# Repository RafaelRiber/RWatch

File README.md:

# RWatch
 
  <p align="center">
 
 <em>Early render of the watch</em>
 
## Short description
The RWatch is a modern and elegant oled "smartwatch" based around the Atmel ATSAMD21-G18A ARM Cortex M0+ Microcontroller, with a 9 DOF IMU and environmental sensing, and everything contained in a PCB the size of the screen.

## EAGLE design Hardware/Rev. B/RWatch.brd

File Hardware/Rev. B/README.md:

### Warning ! Rev B has not been tested. Use at your own risk

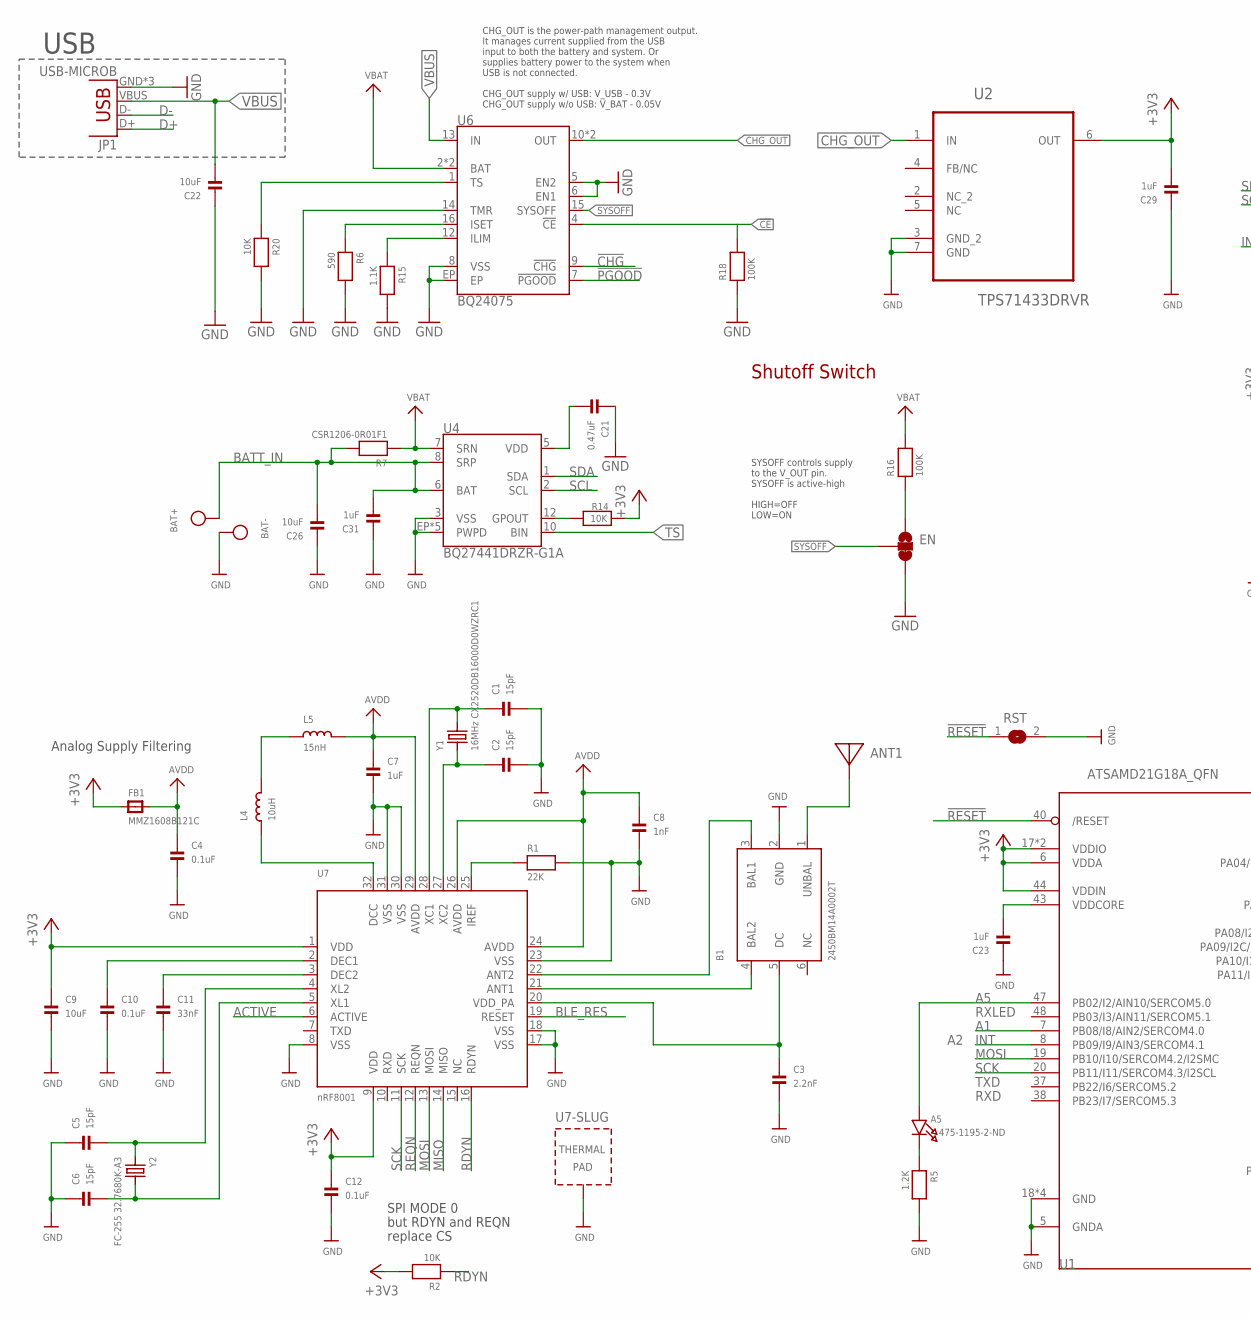
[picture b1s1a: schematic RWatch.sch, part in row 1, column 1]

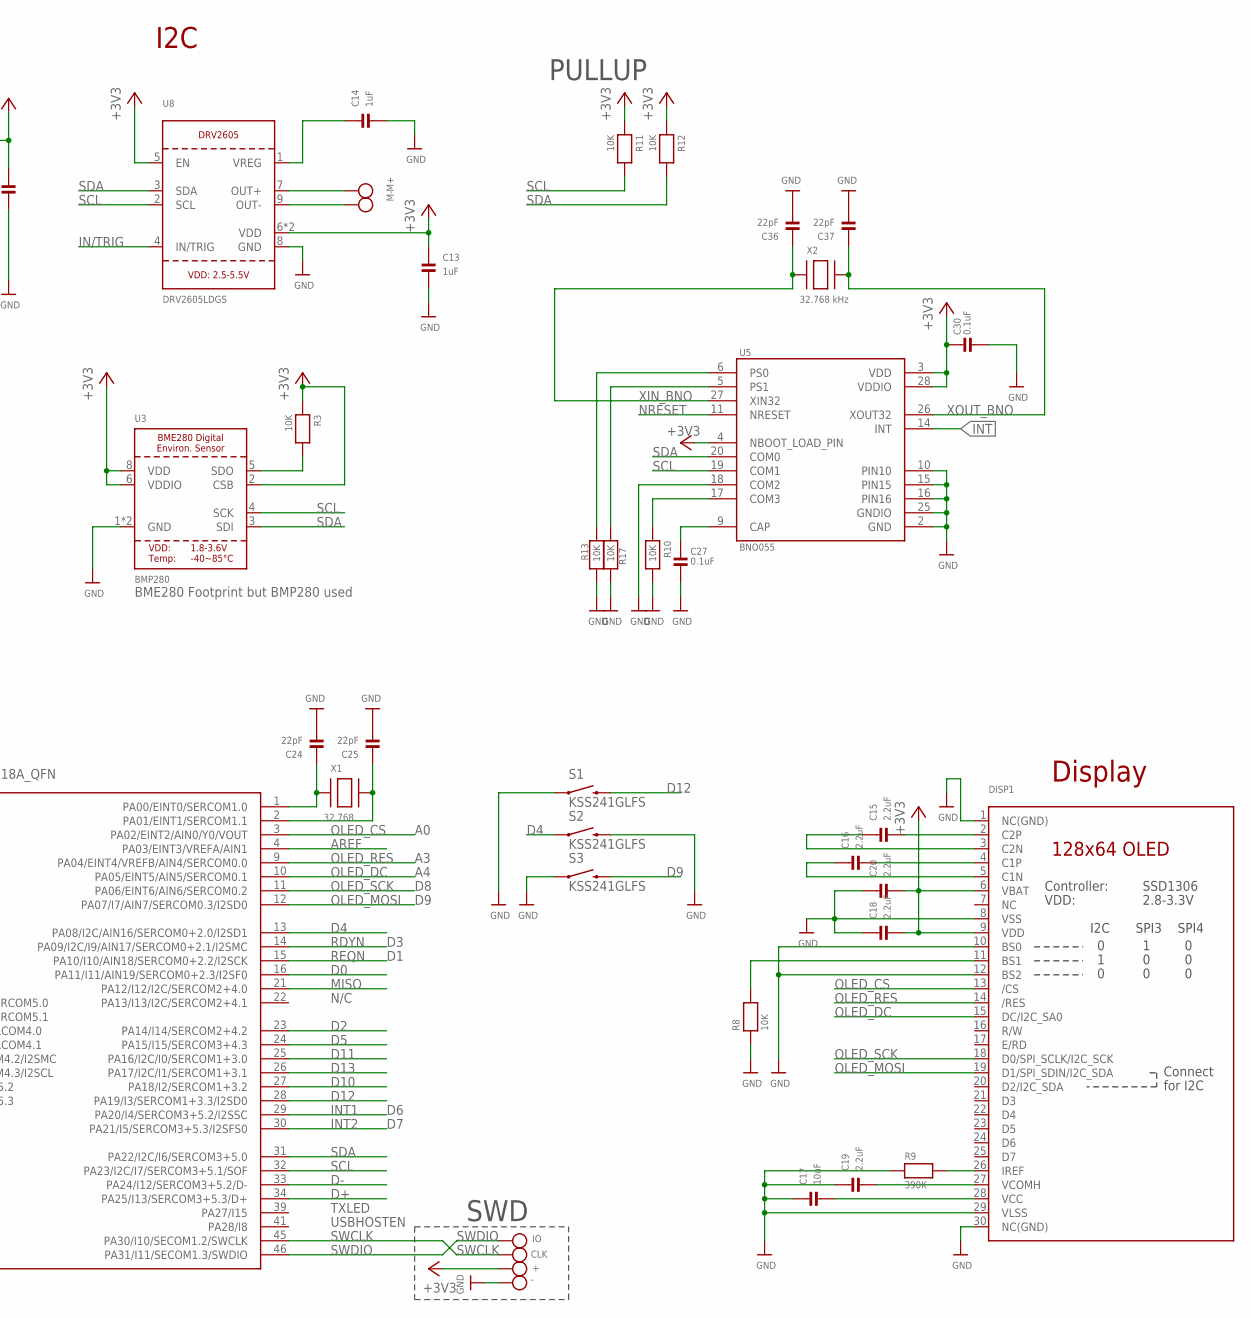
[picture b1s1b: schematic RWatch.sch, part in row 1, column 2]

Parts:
+: TESTPOINTROUND1.5MM; TESTPOINT_ROUND_1.5MM
-: TESTPOINTROUND1.5MM; TESTPOINT_ROUND_1.5MM
A5: 475-1195-2-ND; CHIPLED_0603_NOOUTLINE
ANT1: ANTENNA_PCBNRF8001_1.6MM; ANT_PCB_2.4GHZ_NRF8001_1.6MM_1OZ
B1: 2450BM14A0002T; BALUN0603
BAT+: TESTPOINTROUND2MM; TESTPOINT_ROUND_2MM
BAT-: TESTPOINTROUND2MM; TESTPOINT_ROUND_2MM
C1, C2, C5, C6: 15pF; 0402
C3: 2.2nF; 0402
C4, C10, C12, C27, C30: 0.1uF; 0402
C7, C13, C14, C23, C29, C31: 1uF; 0402
C8: 1nF; 0402
C9: 10uF; 0402
C11: 33nF; 0402
C15, C16, C18, C19, C20: 2.2uF; 0402
C17, C22, C26: 10uF; 0603
C21: 0.47uF; 0402
C24, C25, C36, C37: 22pF; 0402
CLK: TESTPOINTROUND1.5MM; TESTPOINT_ROUND_1.5MM
DISP1: DISP_OLED_UG-2864HSWEG01; UG-2864HSWEG01_1.3_WRAPAROUND
EN: JUMPER-PAD-3-2OF3_NC_BY_TRACE_SMALL; PAD-JUMPER-3-2OF3_NC_BY_TRACE_YES_SILK_FULL_BOX
FB1: MMZ1608B121C; 0805
IO: TESTPOINTROUND1.5MM; TESTPOINT_ROUND_1.5MM
JP1: USB-MICROB; MPN 10104110-0001LF
L4: 10uH; _0603
L5: 15nH; _0603
M+: TESTPOINTROUND2MM; TESTPOINT_ROUND_2MM
M-: TESTPOINTROUND2MM; TESTPOINT_ROUND_2MM
R1: 22K; 0402
R2, R8: 10K; 0402
R3, R10, R11, R12, R13, R14, R17, R20: 10K; 0402; MPN CRCW060310K0FKEA
R5: 1.2K; 0402; MPN MC0063W06031221R
R6: 590; 0402; MPN CRCW060310K0FKEA
R7: CSR1206-0R01F1; 1206
R9: 390K; 0402
R15: 1.1K; 0402; MPN CRCW060310K0FKEA
R16, R18: 100K; 0402; MPN MC0063W06031221R
RST: SOLDERJUMPERREFLOW; SOLDERJUMPER_REFLOW
S1, S2, S3: KSS241GLFS
U1: ATSAMD21G18A_QFN; TQFN48_7MM
U2: TPS71433DRVR; SON65P200X200X80-7N
U3: BMP280; BME280
U4: BQ27441DRZR-G1A; PDSO-N12
U5: BNO055; LGA28R50P4X10_380X520X100
U6: BQ24075; PVQFN-N16
U7: nRF8001; QFN32_5MM
U8: DRV2605LDGS; PSOP10
X1: 32.768; XTAL3215
X2: 32.768 kHz; XTAL3215
Y1: 16MHz CX2520DB16000D0WZRC1; CRYSTAL_2.5X2
Y2: FC-255 32.7680K-A3; CRYSTAL_4.9X1.8

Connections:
!CE!: R18.2, U6.4 (!CE!)
!CHG!: U6.9 (!CHG!)
!PGOOD!: U6.7 (!PGOOD!)
!RESET: RST.1, U1.40 (/RESET)
+3V3: +.P$1, C9.1, C12.1, C13.1, C18.2, C20.2, C29.2, C30.2, DISP1.6 (VBAT), DISP1.9 (VDD), FB1.1, R2.2, R3.1, R11.1, R12.1, R14.1, U1.6 (VDDA), U1.17 (VDDIO), U1.36 (VDDIO), U1.44 (VDDIN), U2.6 (OUT), U3.2 (CSB), U3.6 (VDDIO), U3.8 (VDD), U5.3 (VDD), U5.4 (NBOOT_LOAD_PIN), U5.28 (VDDIO), U7.1 (VDD), U7.9 (VDD), U8.5 (EN), U8.6 (VDD), U8.10 (VDD)
A1: U1.7 (PB08/I8/AIN2/SERCOM4.0)
A5: A5.A, U1.47 (PB02/I2/AIN10/SERCOM5.0)
ACTIVE: U7.6 (ACTIVE)
AREF: U1.4 (PA03/EINT3/VREFA/AIN1)
AVDD: C4.1, C7.1, C8.1, FB1.2, L5.2, U7.24 (AVDD), U7.26 (AVDD), U7.29 (AVDD)
BATT_IN: BAT+.P$1, C26.2, C31.2, R7.2, U4.6 (BAT), U4.8 (SRP)
BLE_RES: U7.19 (RESET)
CHG_OUT: U2.1 (IN), U6.10 (OUT), U6.11 (OUT)
D0: U1.16 (PA11/I11/AIN19/SERCOM0+2.3/I2SF0)
D2: U1.23 (PA14/I14/SERCOM2+4.2)
D4: S2.1, U1.13 (PA08/I2C/AIN16/SERCOM0+2.0/I2SD1)
D5: U1.24 (PA15/I15/SERCOM3+4.3)
D9: S3.2
D10: U1.27 (PA18/I2/SERCOM1+3.2)
D11: U1.25 (PA16/I2C/I0/SERCOM1+3.0)
D12: S1.2, U1.28 (PA19/I3/SERCOM1+3.3/I2SD0)
D13: U1.26 (PA17/I2C/I1/SERCOM1+3.1)
D+: JP1.D+, U1.34 (PA25/I13/SERCOM3+5.3/D+)
D-: JP1.D-, U1.33 (PA24/I12/SERCOM3+5.2/D-)
GND: -.P$1, B1.2 (GND), BAT-.P$1, C1.2, C2.2, C3.2, C4.2, C5.1, C6.1, C7.2, C8.2, C9.2, C10.2, C11.2, C12.2, C13.2, C14.2, C17.1, C18.1, C19.1, C20.1, C21.1, C22.1, C23.1, C24.2, C25.2, C26.1, C27.1, C29.1, C30.1, C31.1, C36.2, C37.2, DISP1.1 (NC(GND)), DISP1.8 (VSS), DISP1.10 (BS0), DISP1.12 (BS2), DISP1.29 (VLSS), DISP1.30 (NC(GND)), EN.3, JP1.GND, JP1.MT1 (GND), JP1.MT2 (GND), R1.2, R5.2, R6.2, R8.1, R9.1, R10.2, R13.2, R15.2, R17.2, R18.1, R20.2, RST.2, S1.1, S2.2, S3.1, U1.5 (GNDA), U1.18 (GND), U1.35 (GND), U1.42 (GND), U1.THERMAL (GND), U2.3 (GND_2), U2.7 (GND), U3.1 (GND), U3.7 (GND), U4.3 (VSS), U4.EP (PWPD), U4.EP1 (PWPD), U4.EP2 (PWPD), U4.EP3 (PWPD), U4.EP4 (PWPD), U5.2 (GND), U5.10 (PIN10), U5.15 (PIN15), U5.16 (PIN16), U5.18 (COM2), U5.25 (GNDIO), U6.5 (EN2), U6.6 (EN1), U6.8 (VSS), U6.14 (TMR), U6.EP, U7.8 (VSS), U7.17 (VSS), U7.18 (VSS), U7.23 (VSS), U7.30 (VSS), U7.31 (VSS), U7.33 (TP), U8.8 (GND)
ILIM: R15.1, U6.12 (ILIM)
IN/TRIG: U8.4 (IN/TRIG)
INT: U1.8 (PB09/I9/AIN3/SERCOM4.1), U5.14 (INT)
INT1: U1.29 (PA20/I4/SERCOM3+5.2/I2SSC)
INT2: U1.30 (PA21/I5/SERCOM3+5.3/I2SFS0)
ISET: R6.1, U6.16 (ISET)
MISO: U1.21 (PA12/I12/I2C/SERCOM2+4.0), U7.14 (MISO)
MOSI: U1.19 (PB10/I10/SERCOM4.2/I2SMC), U7.13 (MOSI)
unnamed: ANT1.FEED, B1.1 (UNBAL)
unnamed: B1.3 (BAL1), U7.22 (ANT2)
unnamed: B1.4 (BAL2), U7.21 (ANT1)
unnamed: B1.5 (DC), C3.1, U7.20 (VDD_PA)
unnamed: L4.2, L5.1
unnamed: DISP1.11 (BS1), R8.2
unnamed: C11.1, U7.3 (DEC2)
unnamed: C10.1, U7.2 (DEC1)
unnamed: C1.1, U7.28 (XC1), Y1.3 (2)
unnamed: C2.1, U7.27 (XC2), Y1.1
unnamed: L4.1, U7.32 (DCC)
unnamed: R1.1, U7.25 (IREF)
unnamed: C21.2, U4.5 (VDD)
unnamed: C24.1, U1.1 (PA00/EINT0/SERCOM1.0), X1.P$1
unnamed: C25.1, U1.2 (PA01/EINT1/SERCOM1.1), X1.P$2
unnamed: R3.2, U3.5 (SDO)
unnamed: C14.1, U8.1 (VREG)
unnamed: R14.2, U4.12 (GPOUT)
unnamed: C5.2, U7.4 (XL2), Y2.1
unnamed: C6.2, U7.5 (XL1), Y2.2
unnamed: EN.1, R16.1
unnamed: A5.C, R5.1
unnamed: C27.2, U5.9 (CAP)
unnamed: R10.1, U5.17 (COM3)
unnamed: R17.1, U5.5 (PS1)
unnamed: R13.1, U5.6 (PS0)
unnamed: DISP1.26 (IREF), R9.2
unnamed: C15.2, DISP1.2 (C2P)
unnamed: C15.1, DISP1.3 (C2N)
unnamed: C16.2, DISP1.4 (C1P)
unnamed: C16.1, DISP1.5 (C1N)
unnamed: C17.2, DISP1.28 (VCC)
unnamed: C19.2, DISP1.27 (VCOMH)
NRESET: U5.11 (NRESET)
OLED_CS: DISP1.13 (/CS), U1.3 (PA02/EINT2/AIN0/Y0/VOUT)
OLED_DC: DISP1.15 (DC/I2C_SA0), U1.10 (PA05/EINT5/AIN5/SERCOM0.1)
OLED_MOSI: DISP1.19 (D1/SPI_SDIN/I2C_SDA), U1.12 (PA07/I7/AIN7/SERCOM0.3/I2SD0)
OLED_RES: DISP1.14 (/RES), U1.9 (PA04/EINT4/VREFB/AIN4/SERCOM0.0)
OLED_SCK: DISP1.18 (D0/SPI_SCLK/I2C_SCK), U1.11 (PA06/EINT6/AIN6/SERCOM0.2)
OUT+: M+.P$1, U8.7 (OUT+)
OUT-: M-.P$1, U8.9 (OUT-)
RDYN: R2.1, U1.14 (PA09/I2C/I9/AIN17/SERCOM0+2.1/I2SMC), U7.16 (RDYN)
REQN: U1.15 (PA10/I10/AIN18/SERCOM0+2.2/I2SCK), U7.12 (REQN)
SCK: U1.20 (PB11/I11/SERCOM4.3/I2SCL), U7.11 (SCK)
SCL: R11.2, U1.32 (PA23/I2C/I7/SERCOM3+5.1/SOF), U3.4 (SCK), U4.2 (SCL), U5.19 (COM1), U8.2 (SCL)
SDA: R12.2, U1.31 (PA22/I2C/I6/SERCOM3+5.0), U3.3 (SDI), U4.1 (SDA), U5.20 (COM0), U8.3 (SDA)
SWCLK: CLK.P$1, U1.45 (PA30/I10/SECOM1.2/SWCLK)
SWDIO: IO.P$1, U1.46 (PA31/I11/SECOM1.3/SWDIO)
SYSOFF: EN.2, U6.15 (SYSOFF)
TS: R20.1, U4.10 (BIN), U6.1 (TS)
VBAT: R7.1, R16.2, U4.7 (SRN), U6.2 (BAT), U6.3 (BAT)
VBUS: C22.2, JP1.VBUS, U6.13 (IN)
VDDCORE1: C23.2, U1.43 (VDDCORE)
XIN_BNO: C36.1, U5.27 (XIN32), X2.P$1
XOUT_BNO: C37.1, U5.26 (XOUT32), X2.P$2

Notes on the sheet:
Analog Supply Filtering
SPI MODE 0
but RDYN and REQN
replace CS
SWD
Display
PULLUP
N/C
TXLED
USBHOSTEN
RXLED
TXD
RXD
USB
I2C
CHG_OUT is the power-path management output. It manages current supplied from the USB input to both the battery and system. Or supplies battery power to the system when USB is not connected. CHG_OUT supply w/ USB: V_USB - 0.3V CHG_OUT supply w/o USB: V_BAT - 0.05V
Shutoff Switch
SYSOFF controls supply to the V_OUT pin. SYSOFF is active-high HIGH=OFF LOW=ON
BME280 Footprint but BMP280 used

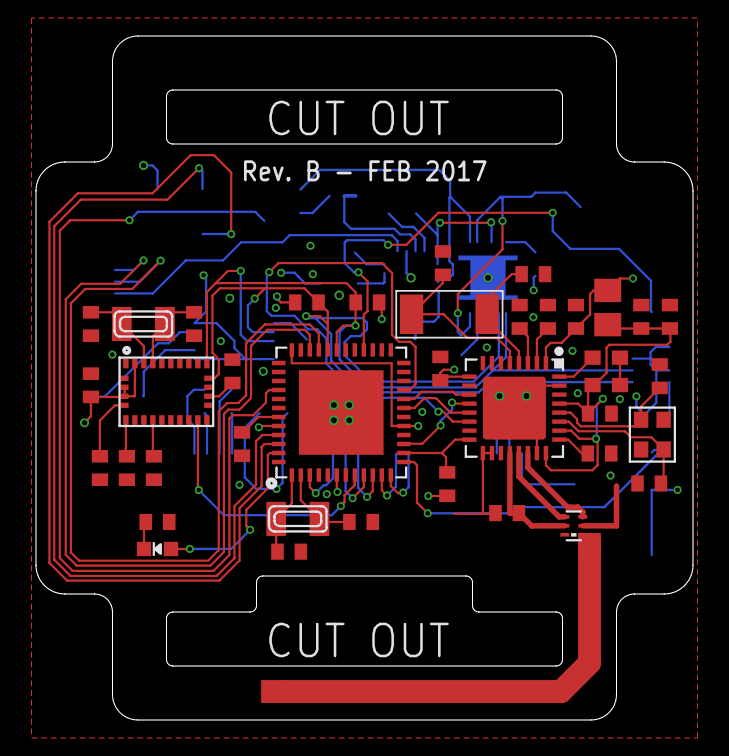
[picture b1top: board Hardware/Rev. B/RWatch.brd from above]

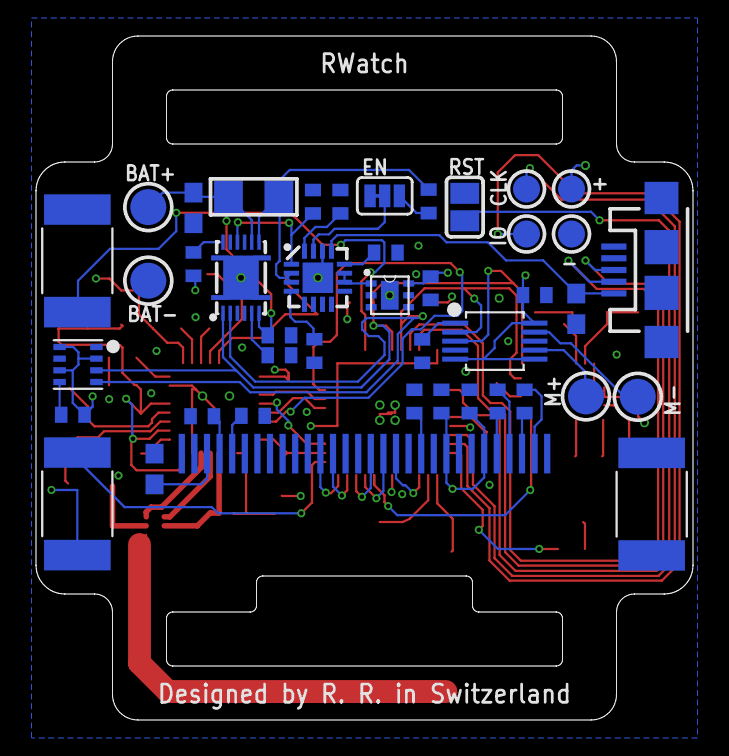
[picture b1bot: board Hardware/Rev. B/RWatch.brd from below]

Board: 4 copper layers, 36.5 x 38.0 mm, 83 parts (42 on the bottom side), 71 nets.

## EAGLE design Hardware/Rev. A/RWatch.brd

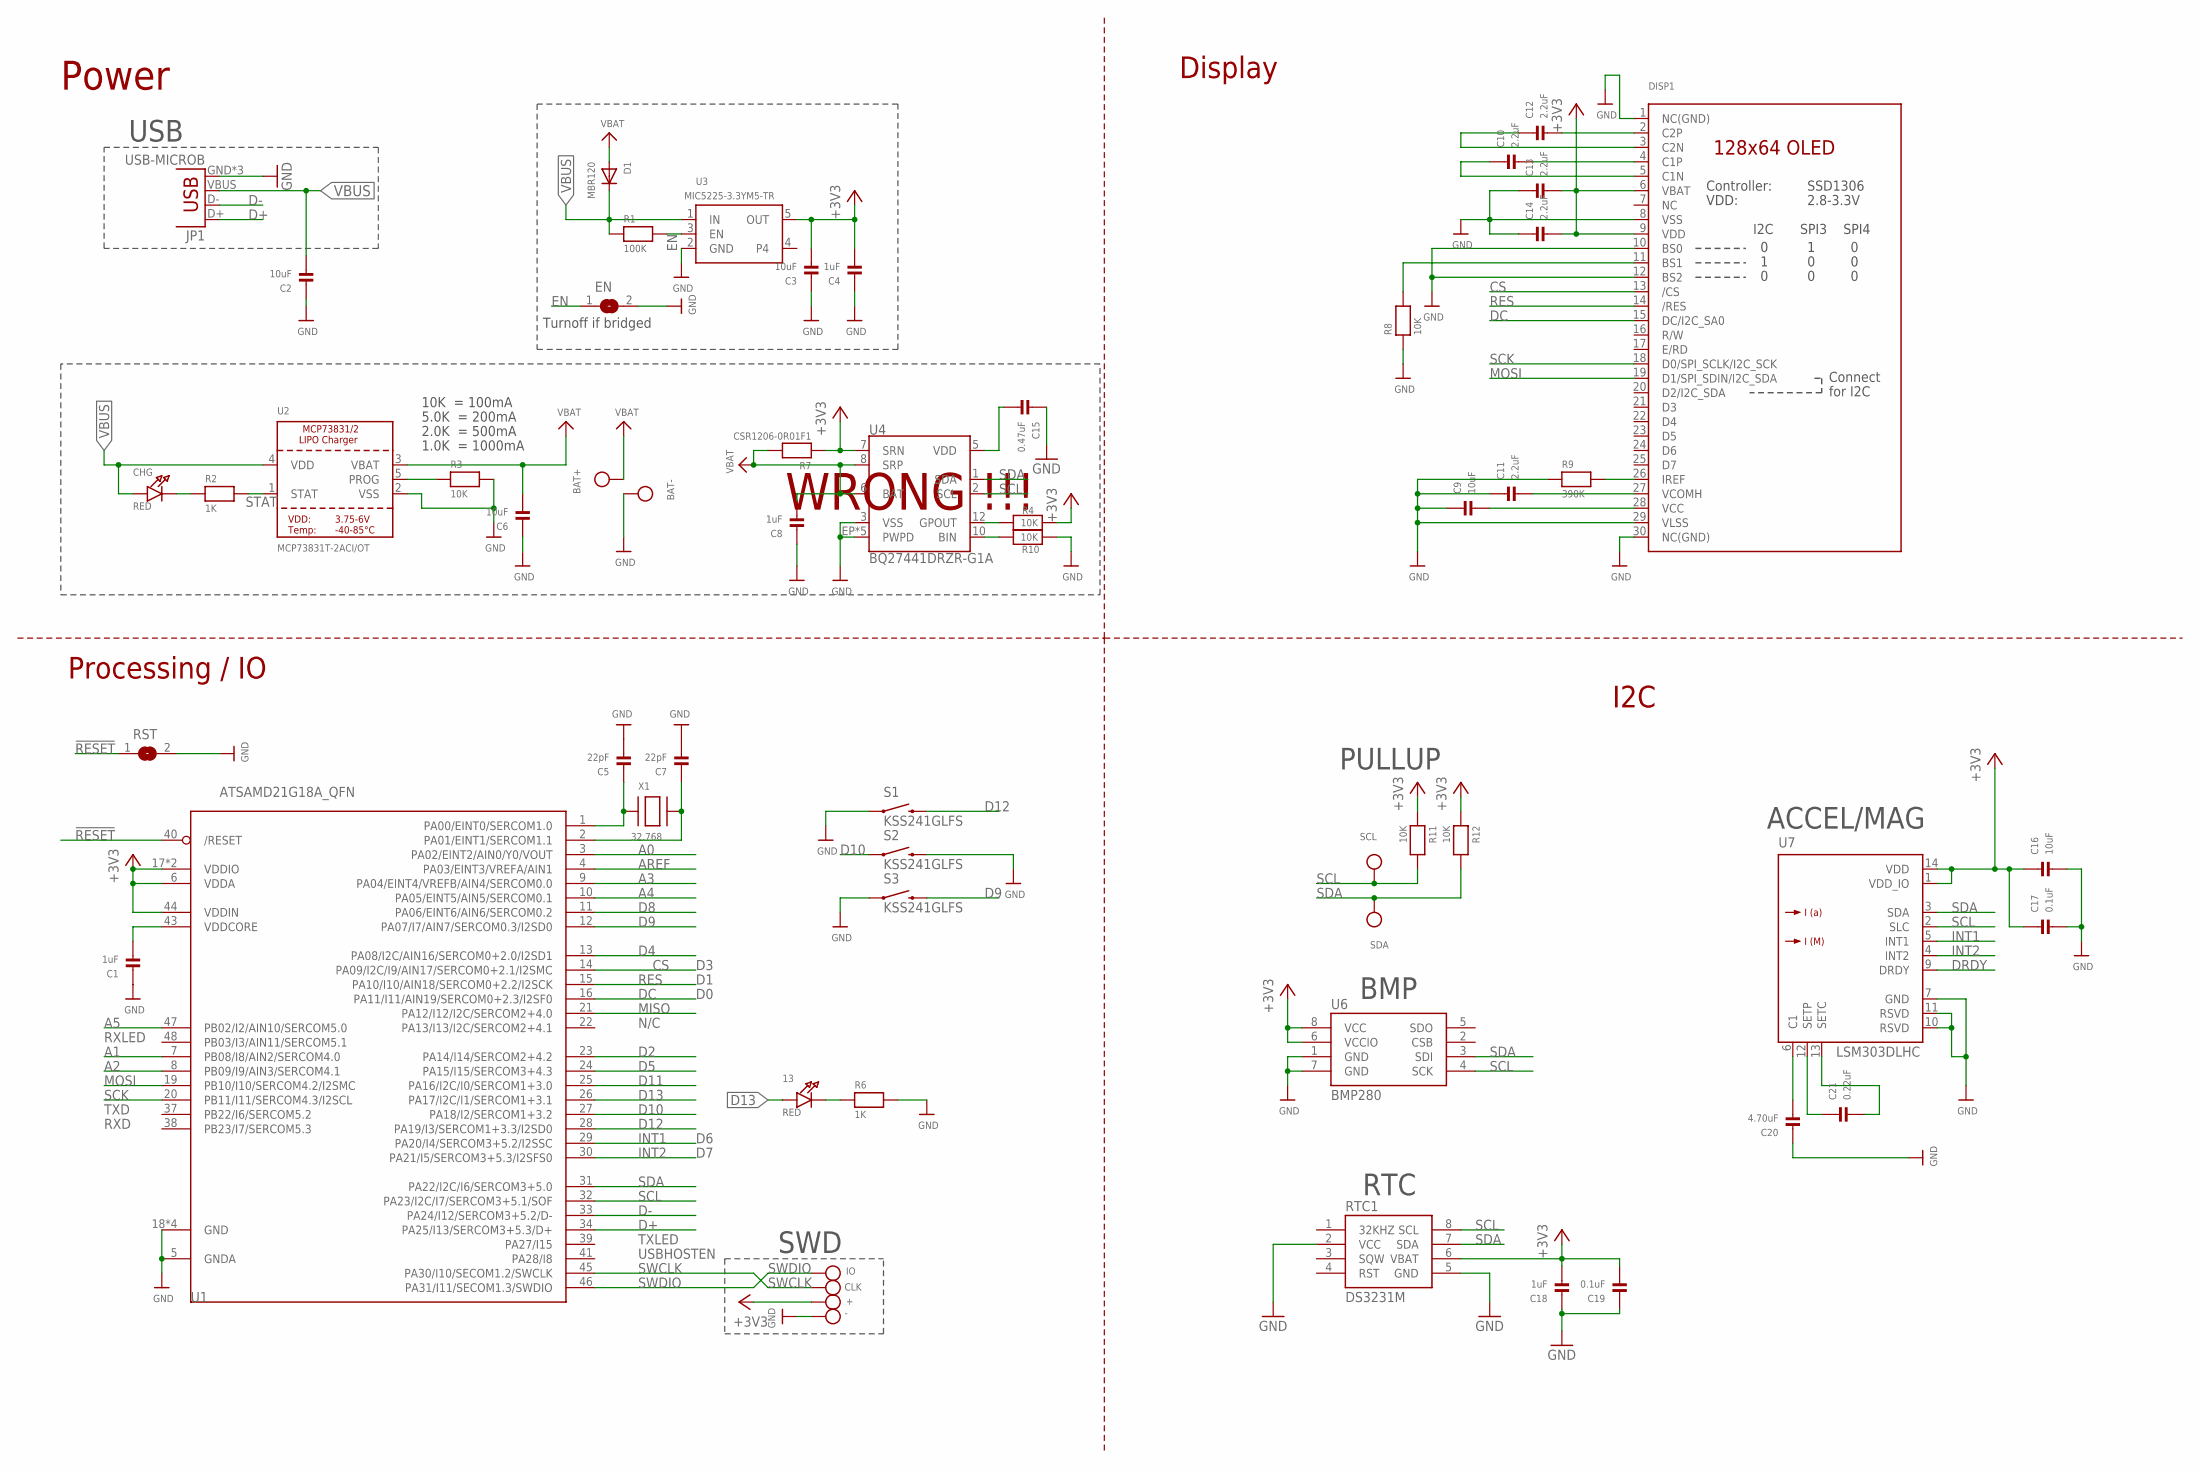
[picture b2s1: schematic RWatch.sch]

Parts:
13: RED; CHIPLED_0805; MPN LGQ971
+: TESTPOINTROUND1MM; TESTPOINT_ROUND_1MM
-: TESTPOINTROUND1MM; TESTPOINT_ROUND_1MM
BAT+: TESTPOINTROUND2MM; TESTPOINT_ROUND_2MM
BAT-: TESTPOINTROUND2MM; TESTPOINT_ROUND_2MM
C1, C4, C8, C18: 1uF; 0402
C2, C3, C6, C9, C16: 10uF; 0603
C5, C7: 22pF; 0402
C10, C11, C12, C13, C14: 2.2uF; 0402
C15: 0.47uF; 0402
C17, C19: 0.1uF; 0402
C20: 4.70uF; 0402
C21: 0.22uF; 0402
CHG: RED; CHIPLED_0805; MPN LGQ971
CLK: TESTPOINTROUND1MM; TESTPOINT_ROUND_1MM
D1: MBR120; SOD-123; MPN MBR120VLSFT1G
DISP1: DISP_OLED_UG-2864HSWEG01; UG-2864HSWEG01_1.3_WRAPAROUND
EN: SOLDERJUMPERREFLOW_NOPASTE; SOLDERJUMPER_REFLOW_NOPASTE
IO: TESTPOINTROUND1MM; TESTPOINT_ROUND_1MM
JP1: USB-MICROB; MPN 10104110-0001LF
R1: 100K; 0402; MPN MC0063W06031221R
R2: 1K; 0402; MPN MC0063W06031221R
R3: 10K; 0402; MPN CRCW060310K0JNEA
R4, R10, R11, R12: 10K; 0402; MPN CRCW060310K0FKEA
R6: 1K; 0402; MPN CRCW06032K20JNEA
R7: CSR1206-0R01F1; 1206
R8: 10K; 0402
R9: 390K; 0402
RST: SOLDERJUMPERREFLOW_NOPASTE; SOLDERJUMPER_REFLOW_NOPASTE
RTC1: DS3231M; SOIC8; MPN DS3231MZ+TRL
S1, S2, S3: KSS241GLFS
SCL: TESTPOINTROUND1MM; TESTPOINT_ROUND_1MM
SDA: TESTPOINTROUND1MM; TESTPOINT_ROUND_1MM
U1: ATSAMD21G18A_QFN; TQFN48_7MM
U2: MCP73831T-2ACI/OT; SOT23-5@1; MPN MCP73831T-2ACI/OT
U3: MIC5225-3.3YM5-TR; SOT23-5; MPN MIC5225-3.3YM5-TR
U4: BQ27441DRZR-G1A; PDSO-N12
U6: BMP280; LGA8
U7: LSM303DLHC; LGA-14
X1: 32.768; XTAL3215

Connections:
!RESET: RST.1, U1.40 (/RESET)
+3V3: +.P$1, C3.2, C4.2, C13.2, C14.2, C16.1, C17.1, C18.2, C19.2, DISP1.6 (VBAT), DISP1.9 (VDD), R4.1, R7.1, R11.1, R12.1, RTC1.6 (VBAT), U1.6 (VDDA), U1.17 (VDDIO), U1.36 (VDDIO), U1.44 (VDDIN), U3.5 (OUT), U4.7 (SRN), U6.6 (VCCIO), U6.8 (VCC), U7.1 (VDD_IO), U7.14 (VDD)
A0: U1.3 (PA02/EINT2/AIN0/Y0/VOUT)
A1: U1.7 (PB08/I8/AIN2/SERCOM4.0)
A2: U1.8 (PB09/I9/AIN3/SERCOM4.1)
A3: U1.9 (PA04/EINT4/VREFB/AIN4/SERCOM0.0)
A4: U1.10 (PA05/EINT5/AIN5/SERCOM0.1)
A5: U1.47 (PB02/I2/AIN10/SERCOM5.0)
AREF: U1.4 (PA03/EINT3/VREFA/AIN1)
BIN: R10.2, U4.10 (BIN)
CS: DISP1.13 (/CS), U1.14 (PA09/I2C/I9/AIN17/SERCOM0+2.1/I2SMC)
D2: U1.23 (PA14/I14/SERCOM2+4.2)
D4: U1.13 (PA08/I2C/AIN16/SERCOM0+2.0/I2SD1)
D5: U1.24 (PA15/I15/SERCOM3+4.3)
D8: U1.11 (PA06/EINT6/AIN6/SERCOM0.2)
D9: S3.2, U1.12 (PA07/I7/AIN7/SERCOM0.3/I2SD0)
D10: S2.1, U1.27 (PA18/I2/SERCOM1+3.2)
D11: U1.25 (PA16/I2C/I0/SERCOM1+3.0)
D12: S1.2, U1.28 (PA19/I3/SERCOM1+3.3/I2SD0)
D13: 13.A, U1.26 (PA17/I2C/I1/SERCOM1+3.1)
D+: JP1.D+, U1.34 (PA25/I13/SERCOM3+5.3/D+)
D-: JP1.D-, U1.33 (PA24/I12/SERCOM3+5.2/D-)
DC: DISP1.15 (DC/I2C_SA0), U1.16 (PA11/I11/AIN19/SERCOM0+2.3/I2SF0)
DRDY: U7.9 (DRDY)
EN: EN.1, R1.2, U3.3 (EN)
GND: -.P$1, BAT-.P$1, C1.1, C2.1, C3.1, C4.1, C5.2, C6.1, C7.2, C8.1, C9.1, C11.1, C13.1, C14.1, C15.1, C16.2, C17.2, C18.1, C19.1, C20.1, DISP1.1 (NC(GND)), DISP1.8 (VSS), DISP1.10 (BS0), DISP1.12 (BS2), DISP1.29 (VLSS), DISP1.30 (NC(GND)), EN.2, JP1.GND, JP1.MT1 (GND), JP1.MT2 (GND), R3.2, R6.2, R8.1, R9.1, R10.1, RST.2, RTC1.2 (VCC), RTC1.5 (GND), S1.1, S2.2, S3.1, U1.5 (GNDA), U1.18 (GND), U1.35 (GND), U1.42 (GND), U1.THERMAL (GND), U2.2 (VSS), U3.2 (GND), U4.3 (VSS), U4.EP (PWPD), U4.EP1 (PWPD), U4.EP2 (PWPD), U4.EP3 (PWPD), U4.EP4 (PWPD), U6.1 (GND), U6.7 (GND), U7.7 (GND), U7.10 (RSVD), U7.11 (RSVD)
INT1: U1.29 (PA20/I4/SERCOM3+5.2/I2SSC), U7.5 (INT1)
INT2: U1.30 (PA21/I5/SERCOM3+5.3/I2SFS0), U7.4 (INT2)
MISO: U1.21 (PA12/I12/I2C/SERCOM2+4.0)
MOSI: DISP1.19 (D1/SPI_SDIN/I2C_SDA), U1.19 (PB10/I10/SERCOM4.2/I2SMC)
unnamed: DISP1.11 (BS1), R8.2
unnamed: C15.2, U4.5 (VDD)
unnamed: C5.1, U1.1 (PA00/EINT0/SERCOM1.0), X1.P$1
unnamed: C7.1, U1.2 (PA01/EINT1/SERCOM1.1), X1.P$2
unnamed: CHG.C, R2.1
unnamed: C20.2, U7.6 (C1)
unnamed: C21.1, U7.12 (SETP)
unnamed: C21.2, U7.13 (SETC)
unnamed: R4.2, U4.12 (GPOUT)
unnamed: 13.C, R6.1
unnamed: DISP1.26 (IREF), R9.2
unnamed: C12.2, DISP1.2 (C2P)
unnamed: C12.1, DISP1.3 (C2N)
unnamed: C10.2, DISP1.4 (C1P)
unnamed: C10.1, DISP1.5 (C1N)
unnamed: C9.2, DISP1.28 (VCC)
unnamed: C11.2, DISP1.27 (VCOMH)
PROG: R3.1, U2.5 (PROG)
RES: DISP1.14 (/RES), U1.15 (PA10/I10/AIN18/SERCOM0+2.2/I2SCK)
SCK: DISP1.18 (D0/SPI_SCLK/I2C_SCK), U1.20 (PB11/I11/SERCOM4.3/I2SCL)
SCL: R11.2, RTC1.8 (SCL), SCL.P$1, U1.32 (PA23/I2C/I7/SERCOM3+5.1/SOF), U4.2 (SCL), U6.4 (SCK), U7.2 (SLC)
SDA: R12.2, RTC1.7 (SDA), SDA.P$1, U1.31 (PA22/I2C/I6/SERCOM3+5.0), U4.1 (SDA), U6.3 (SDI), U7.3 (SDA)
STAT: R2.2, U2.1 (STAT)
SWCLK: CLK.P$1, U1.45 (PA30/I10/SECOM1.2/SWCLK)
SWDIO: IO.P$1, U1.46 (PA31/I11/SECOM1.3/SWDIO)
VBAT: BAT+.P$1, C6.2, C8.2, D1.A, R7.2, U2.3 (VBAT), U4.6 (BAT), U4.8 (SRP)
VBUS: C2.2, CHG.A, D1.C, JP1.VBUS, R1.1, U2.4 (VDD), U3.1 (IN)
VDDCORE1: C1.2, U1.43 (VDDCORE)

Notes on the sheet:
SWD
Display
BMP
PULLUP
N/C
TXLED
USBHOSTEN
RXLED
TXD
RXD
10K = 100mA
5.0K = 200mA
2.0K = 500mA
1.0K = 1000mA
Power
USB
RTC
ACCEL/MAG
I2C
Processing / IO
Turnoff if bridged
WRONG !!!

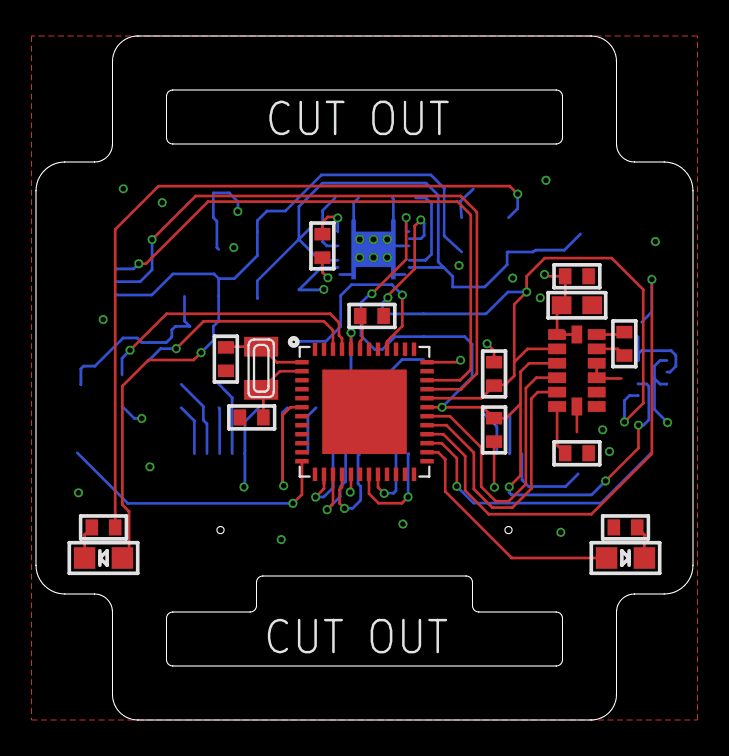
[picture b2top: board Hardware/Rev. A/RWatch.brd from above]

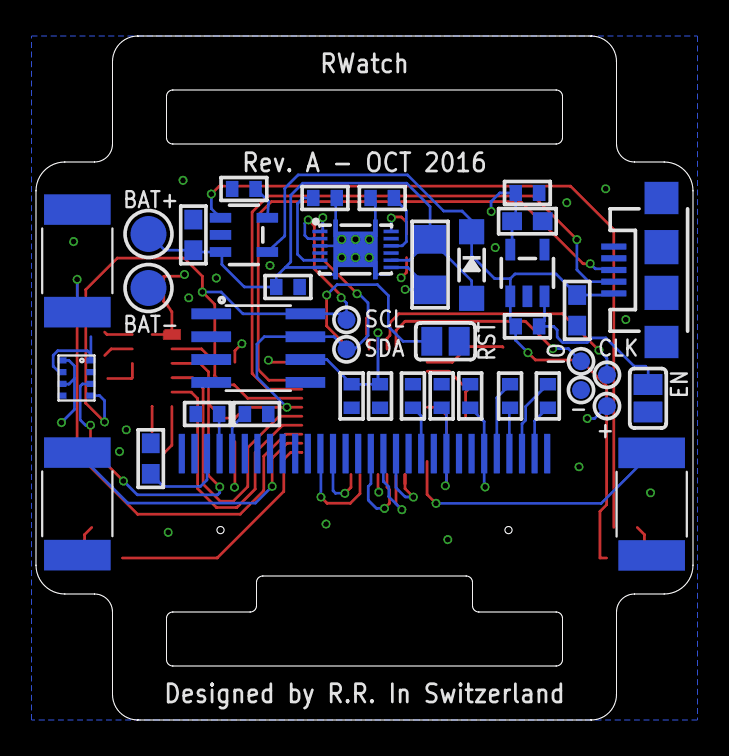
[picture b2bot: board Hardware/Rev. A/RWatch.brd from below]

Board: 4 copper layers, 36.5 x 38.0 mm, 58 parts (40 on the bottom side), 44 nets.

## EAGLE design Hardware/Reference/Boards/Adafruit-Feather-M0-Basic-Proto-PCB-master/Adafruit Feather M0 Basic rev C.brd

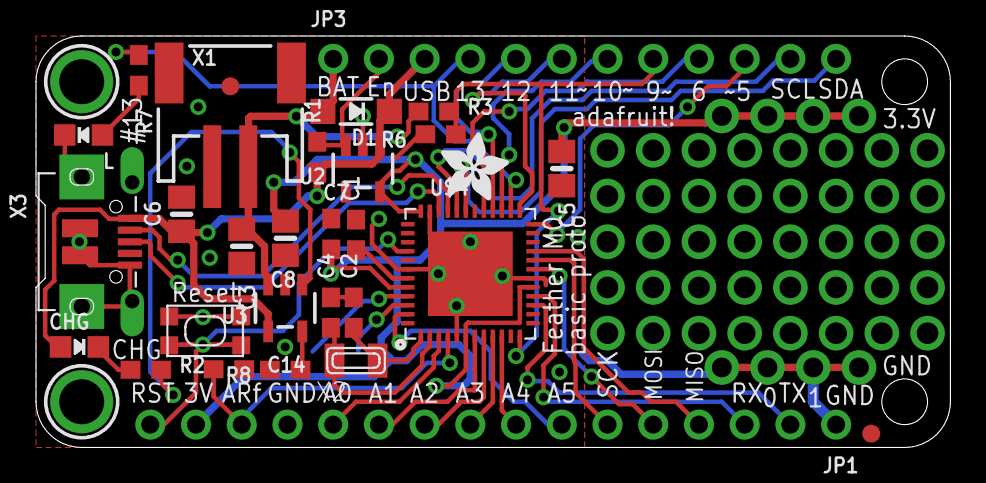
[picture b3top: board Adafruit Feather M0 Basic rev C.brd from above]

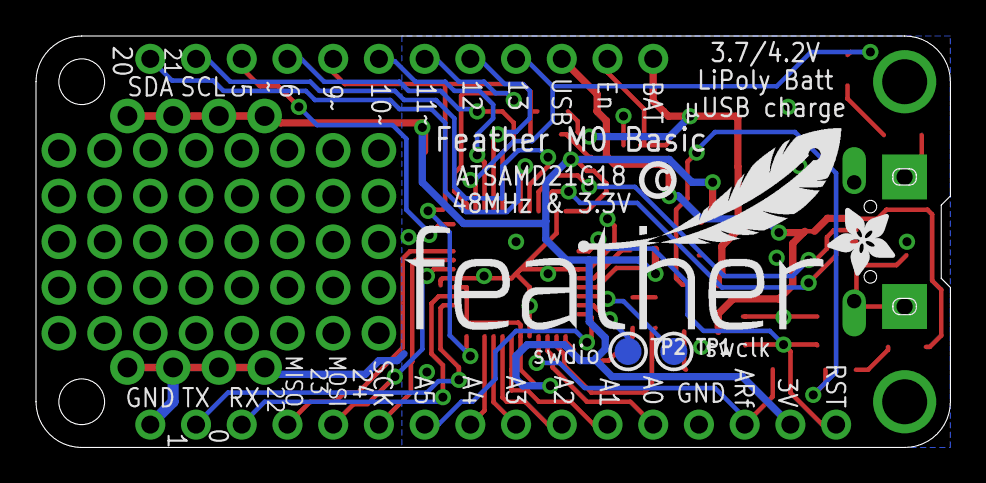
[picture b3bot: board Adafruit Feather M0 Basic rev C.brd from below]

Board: 2 copper layers, 50.8 x 22.9 mm, 37 parts (5 on the bottom side), 38 nets.

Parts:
C1, C7, C14: 1uF; 0603-NO
C2, C4: 22pF; 0603-NO
C3, C6, C8: 10µF; 0805-NO
C5: 10uF; 0805-NO
CHG: ORANGE; CHIPLED_0805_NOOUTLINE
D1: MBR120; SOD-123
JP1: 1X16_ROUND
JP3: 1X12_ROUND
L: RED; CHIPLED_0805_NOOUTLINE
R1, R3: 100k; 0603-NO
R2: 1K; 0603-NO
R6: 100K; 0603-NO
R7: 2.2K; 0603-NO
R8: 10K\; 0603-NO
SW1: SPST_TACT-KMR2; KMR2
TP1, TP2: TESTPOINT_ROUND_1.5MM
U2: SPX3819-3.3; SOT23-5
U3: MCP73831T-2ACI/OT; SOT23-5
U$4: ATSAMD21G18_QFN; TQFN48_7MM
U$7, U$12: ADAFRUIT_3.5MM
U$9: FEATHERLOGO
U$13: PCBFEAT-REV-040
U$31, U$32: MOUNTINGHOLE2.5; MOUNTINGHOLE_2.5_PLATED
U$34, U$35: FIDUCIAL""; FIDUCIAL_1MM
X1: JSTPH; JSTPH2
X2: 32.768; XTAL3215
X3: microUSB; 4UCONN_20329_V2

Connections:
!RESET: JP1.16, SW1.1, SW1.3, U$4.40
+3V3: C5.1, C7.1, C8.1, JP1.15, U2.5, U$4.6, U$4.17, U$4.36, U$4.44
A0: JP1.12, U$4.3
A1: JP1.11, U$4.7
A2: JP1.10, U$4.8
A3: JP1.9, U$4.9
A4: JP1.8, U$4.10
A5: JP1.7, U$4.47
AREF: C14.1, JP1.14, U$4.4
D0: JP1.3, U$4.16
D1: JP1.2, U$4.15
D5: JP3.10, U$4.24
D6: JP3.9, U$4.29
D9: JP3.8, R3.2, R6.1, U$4.12
D10: JP3.7, U$4.27
D11: JP3.6, U$4.25
D12: JP3.5, U$4.28
D13: JP3.4, R7.1, U$4.26
D+: U$4.34, X3.D+
D-: U$4.33, X3.D-
EN: JP3.2, R1.2, U2.3
GND: C1.2, C2.2, C3.2, C4.2, C5.2, C6.2, C7.2, C8.2, C14.2, JP1.1, JP1.13, L.C, R6.2, R8.2, SW1.2, SW1.4, U2.2, U3.2, U$4.5, U$4.18, U$4.35, U$4.42, U$4.THERMAL, X1.1, X3.BASE@1, X3.BASE@2, X3.GND, X3.SPRT@1, X3.SPRT@2, X3.SPRT@3, X3.SPRT@4
MISO: JP1.4, U$4.21
MOSI: JP1.5, U$4.19
unnamed: CHG.C, R2.1
unnamed: L.A, R7.2
unnamed: R2.2, U3.1
unnamed: R8.1, U3.5
unnamed: C2.1, U$4.1, X2.P$1
unnamed: C4.1, U$4.2, X2.P$2
SCK: JP1.6, U$4.20
SCL: JP3.11, U$4.32
SDA: JP3.12, U$4.31
SWCLK: TP1.P$1, U$4.45
SWDIO: TP2.P$1, U$4.46
VBAT: C3.1, D1.A, JP3.1, R3.1, U3.3, X1.2
VBUS: C6.1, CHG.A, D1.C, JP3.3, R1.1, U2.1, U3.4, X3.VBUS
VDDCORE: C1.1, U$4.43

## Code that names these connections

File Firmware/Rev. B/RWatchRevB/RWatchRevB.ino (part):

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Free sercom
Pin  Arduino 'Pin' SERCOM    SERCOM alt
-----------------------------------------
PA18  D10          SERCOM1.2 SERCOM3.2
PA16  D11          SERCOM1.0 SERCOM3.0
PA19  D12          SERCOM1.3 SERCOM3.3
PA17  D13          SERCOM1.1 SERCOM3.1
 */

#include <SPI.h>
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#include <BLEPeripheral.h>
#include <BLEUtil.h>

#define OLED_MOSI   10 //FINAL: ??, PROTO: 10
#define OLED_CLK   11  //FINAL: ??, PROTO: 11
#define OLED_DC    12  //FINAL: ??, PROTO: 12
#define OLED_CS    A0  //FINAL: ??, PROTO: A0
#define OLED_RESET A1  //FINAL: ??, PROTO: A1
#define B1Pin       5  //FINAL: ??, PROTO: 5
#define B2Pin       6  //FINAL: ??, PROTO: 6
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
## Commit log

2016-07-28 Imported Files
2016-07-28 Update Sensor Datasheet
2016-10-03 Imported Bitmaps
2016-10-03 Added datasheets
2016-10-03 Added Logo
2016-10-04 Added more data sheets
2016-11-04 Updated brd
2016-11-04 Added datasheet
2016-11-04 Initial firmware
2016-11-04 Revert "Initial firmware"
    This reverts commit 7344d446994e38cccda72d7284f94b4ed1833ed1.
2016-11-04 Revert "Revert "Initial firmware""
    This reverts commit e97536be538c077792ab8bd13cb232262cd61612.
2016-11-04 Changed directory structure for rev. documentation
2016-11-04 Rev. B initial commit, identical as Rev. A
2016-11-04 Changed IMU to BNO055 and RTC to internal RTC
2016-11-04 Added temperature/pressure, battery monitoring, and haptic vibration
2016-11-04 Added BLE connection and logo on main screen when a connection is made
2016-11-04 Variables and object instances cleanup
2016-11-05 Added notification display
2016-11-05 Added bootloading script
2016-11-16 Name Change
2016-11-16 Created Readme
2016-11-16 Cleanup
2016-11-27 Switched BNO-055 library to Arduino.org NAxisMotion library for interrupt support
2016-11-27 Added BMP280 datasheet
2016-12-14 Added flappy bird game
    Code by https://hackaday.io/project/3981-flappy-bird-on-arduino
2019-12-18 Added PCB files
2019-12-18 Added revA schematic pdf

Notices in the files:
Firmware/Rev. B/RWatchRevB/RWatchRevB.ino:
The MIT License (MIT)
Copyright (c) 2016 Rafael Riber
parts and their libraries:
microbuilder: This work is placed in the public domain, and may be freely used for commercial and non-commercial work with the following conditions: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
SparkFun-PowerIC: Licensing: Creative Commons ShareAlike 4.0 International - https://creativecommons.org/licenses/by-sa/4.0
